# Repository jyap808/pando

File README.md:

# Pando Keyboard

Pando is a wired 58-key column-staggered split keyboard. It uses an integrated MCU design on the STM32 platform (STM32G0B1) with an IO expander (PCA9555) on the secondary half, connected over USB-C.

> [!NOTE]
> 📘 The **[Documentation pages](https://jyap808.github.io/pando)** contain a Build and Firmware guide.

> [!TIP]
> 🚀 Want one? Pre-assembled and PCB-tested kits are available on [Etsy](https://www.etsy.com/listing/4567044197/). Your support helps me keep this project open-source and encourages the development of new models!

## Features

- STM32G0B1KBT6 MCU (64 MHz Cortex-M0+, 144 KB SRAM)
- PCA9555 IO expander on the secondary half
- USB-C split communication with ESD protection on all ports
- Hotswap switch sockets
- Single-sided SMD components for hotplate soldering
- Vial firmware for keymap configuration
- Same key layout as the [Pando58](https://jyap808.github.io/pando58), but as an assembled PCB instead of a DIY kit

## Repository

| Directory | Description |
| --------- | ----------- |
| `kicad/` | Schematics and PCB (left, right, switch plates) |
| `firmware/` | QMK/Vial keyboard definition |
| `ergogen/` | Layout configuration and case/plate generation |
| `case/` | 3D printed case models (FreeCAD) |
| `docs/` | This project's documentation site (built with [Zensical](https://zensical.org/)) |

## Firmware

Pando runs [Vial](https://get.vial.today/) firmware. Precompiled builds are on [GitHub Releases](https://github.com/jyap808/pando/releases) — flash with `dfu-util`, or build from source with the keyboard definition in `firmware/keyboards/`. See [Installing Firmware](https://jyap808.github.io/pando/firmware/installing-firmware/) for details.

## License

[Pando Keyboard](https://github.com/jyap808/pando) © 2026 by [Julian Yap](https://julianyap.com/) is Open Hardware, licensed under [CERN-OHL-S v2](https://ohwr.org/cern_ohl_s_v2.txt). See [LICENSE](LICENSE).

The firmware in `firmware/` is licensed under the [GPL v2](https://www.gnu.org/licenses/old-licenses/gpl-2.0.html).

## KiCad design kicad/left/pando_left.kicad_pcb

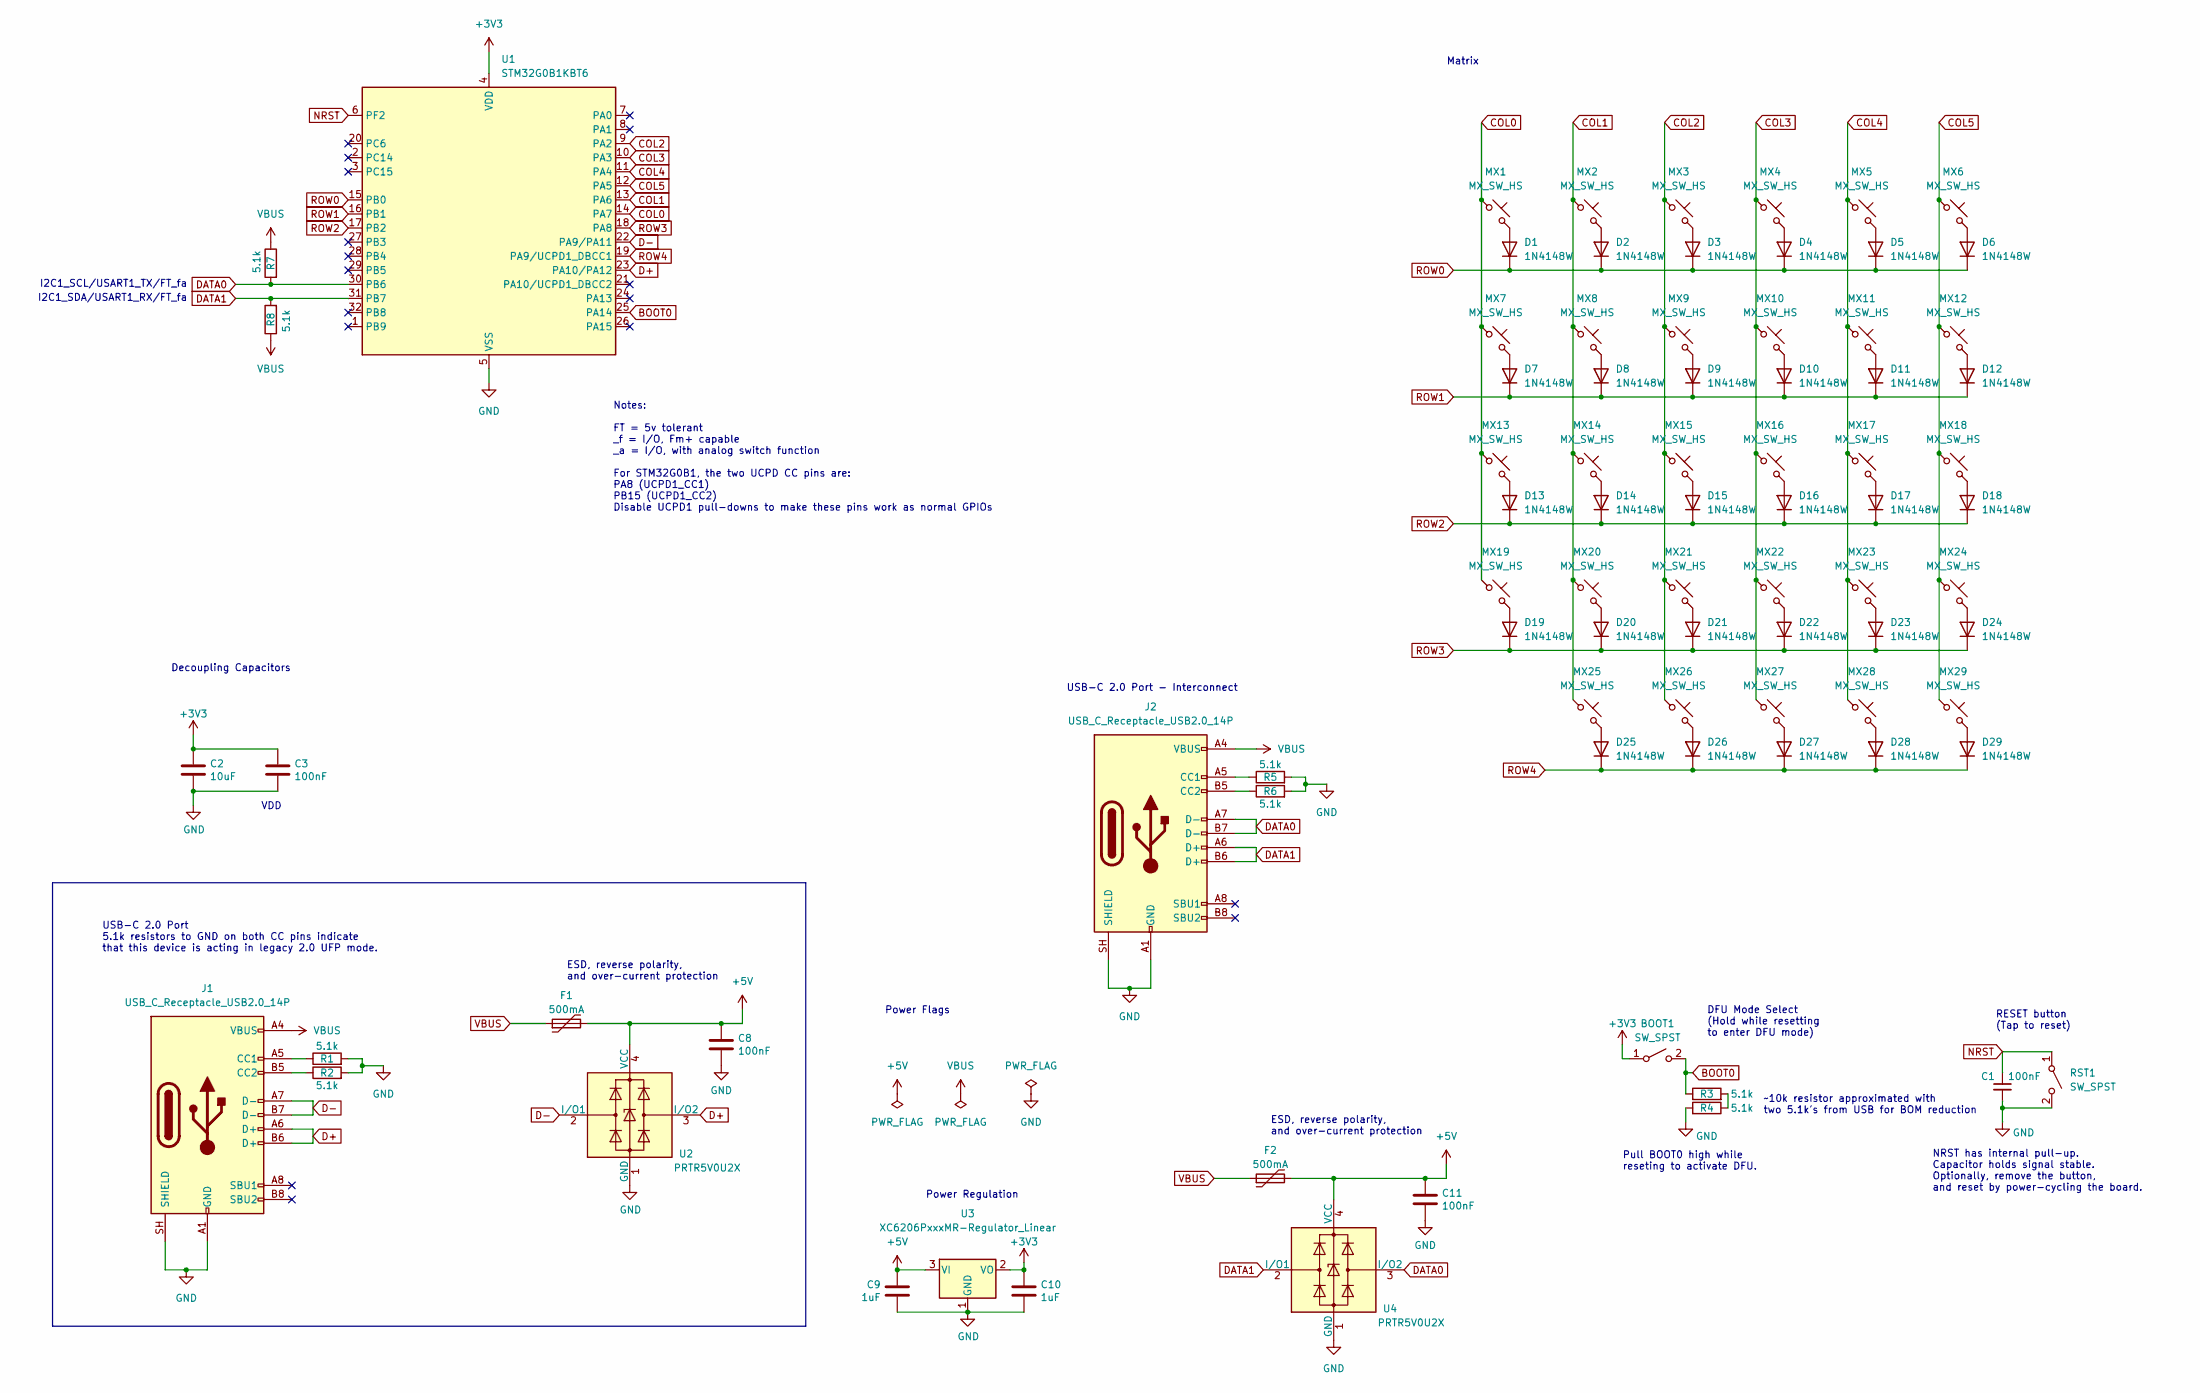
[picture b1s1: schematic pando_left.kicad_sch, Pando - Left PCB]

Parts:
BOOT1: SW_SPST; SW_SPST_TL3342; LCSC C318884
C1, C3, C8, C11: 100nF; C_0603_1608Metric; LCSC C14663
C2: 10uF; C_0603_1608Metric; LCSC C19702
C9, C10: 1uF; C_0603_1608Metric; LCSC C15849
D1, D2, D3, D4, D5, D6, D7, D8, D9, D10, D11, D12, D13, D14, D15, D16, D17, D18, D19, D20, D21, D22, D23, D24, D25, D26, D27, D28, D29: 1N4148W; D_SOD-123; LCSC C81598
F1, F2: 500mA; Fuse_1206_3216Metric; LCSC C135341
J1, J2: USB_C_Receptacle_USB2.0_14P; USB_C_Receptacle_HRO_TYPE-C-31-M-12; LCSC C165948
MX1, MX2, MX3, MX4, MX5, MX6, MX7, MX8, MX9, MX10, MX11, MX12, MX13, MX14, MX15, MX16, MX17, MX18, MX19, MX20, MX21, MX22, MX23, MX24, MX25, MX26, MX27, MX28, MX29: MX_SW_HS; SW_Hotswap_Kailh_MX; LCSC C41430893
R1, R2, R3, R4, R5, R6, R7, R8: 5.1k; R_0603_1608Metric; LCSC C2907114
RST1: SW_SPST; SW_SPST_TL3342; LCSC C318884
U1: STM32G0B1KBT6; LQFP-32_7x7mm_P0.8mm
U2, U4: PRTR5V0U2X; SOT-143; LCSC C2827688
U3: XC6206PxxxMR-Regulator_Linear; SOT-23-3; LCSC C5446

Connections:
+3V3: BOOT1.1 (A), C2.1, C3.1, C10.1, U1.4 (VDD), U3.2 (VO)
+5V: C8.1, C9.1, C11.1, F1.2, F2.2, U2.4 (VCC), U3.3 (VI), U4.4 (VCC)
BOOT0: BOOT1.2 (B), R3.1, U1.25 (PA14)
COL0: MX1.1, MX7.1, MX13.1, MX19.1, U1.14 (PA7)
COL1: MX2.1, MX8.1, MX14.1, MX20.1, MX25.1, U1.13 (PA6)
COL2: MX3.1, MX9.1, MX15.1, MX21.1, MX26.1, U1.9 (PA2)
COL3: MX4.1, MX10.1, MX16.1, MX22.1, MX27.1, U1.10 (PA3)
COL4: MX5.1, MX11.1, MX17.1, MX23.1, MX28.1, U1.11 (PA4)
COL5: MX6.1, MX12.1, MX18.1, MX24.1, MX29.1, U1.12 (PA5)
D+: J1.A6 (D+), J1.B6 (D+), U1.23 (PA10/PA12), U2.3 (I/O2)
D-: J1.A7 (D-), J1.B7 (D-), U1.22 (PA9/PA11), U2.2 (I/O1)
DATA0: J2.A7 (D-), J2.B7 (D-), R7.2, U1.30 (PB6), U4.3 (I/O2)
DATA1: J2.A6 (D+), J2.B6 (D+), R8.2, U1.31 (PB7), U4.2 (I/O1)
GND: C1.2, C2.2, C3.2, C8.2, C9.2, C10.2, C11.2, J1.A1 (GND), J1.A12 (GND), J1.B1 (GND), J1.B12 (GND), J1.SH (SHIELD), J2.A1 (GND), J2.A12 (GND), J2.B1 (GND), J2.B12 (GND), J2.SH (SHIELD), R1.2, R2.2, R4.2, R5.2, R6.2, RST1.2 (B), U1.5 (VSS), U2.1 (GND), U3.1 (GND), U4.1 (GND)
NRST: C1.1, RST1.1 (A), U1.6 (PF2)
unnamed: D1.2 (A), MX1.2
unnamed: D2.2 (A), MX2.2
unnamed: D3.2 (A), MX3.2
unnamed: D4.2 (A), MX4.2
unnamed: D5.2 (A), MX5.2
unnamed: D6.2 (A), MX6.2
unnamed: D7.2 (A), MX7.2
unnamed: D8.2 (A), MX8.2
unnamed: D9.2 (A), MX9.2
unnamed: D10.2 (A), MX10.2
unnamed: D11.2 (A), MX11.2
unnamed: D12.2 (A), MX12.2
unnamed: D13.2 (A), MX13.2
unnamed: D14.2 (A), MX14.2
unnamed: D15.2 (A), MX15.2
unnamed: D16.2 (A), MX16.2
unnamed: D17.2 (A), MX17.2
unnamed: D18.2 (A), MX18.2
unnamed: D19.2 (A), MX19.2
unnamed: D20.2 (A), MX20.2
unnamed: D21.2 (A), MX21.2
unnamed: D22.2 (A), MX22.2
unnamed: D23.2 (A), MX23.2
unnamed: D24.2 (A), MX24.2
unnamed: D25.2 (A), MX25.2
unnamed: D26.2 (A), MX26.2
unnamed: D27.2 (A), MX27.2
unnamed: D28.2 (A), MX28.2
unnamed: D29.2 (A), MX29.2
unnamed: J1.A5 (CC1), R1.1
unnamed: J1.B5 (CC2), R2.1
unnamed: J2.A5 (CC1), R5.1
unnamed: J2.B5 (CC2), R6.1
unnamed: R3.2, R4.1
ROW0: D1.1 (K), D2.1 (K), D3.1 (K), D4.1 (K), D5.1 (K), D6.1 (K), U1.15 (PB0)
ROW1: D7.1 (K), D8.1 (K), D9.1 (K), D10.1 (K), D11.1 (K), D12.1 (K), U1.16 (PB1)
ROW2: D13.1 (K), D14.1 (K), D15.1 (K), D16.1 (K), D17.1 (K), D18.1 (K), U1.17 (PB2)
ROW3: D19.1 (K), D20.1 (K), D21.1 (K), D22.1 (K), D23.1 (K), D24.1 (K), U1.18 (PA8)
ROW4: D25.1 (K), D26.1 (K), D27.1 (K), D28.1 (K), D29.1 (K), U1.19 (PA9/UCPD1_DBCC1)
VBUS: F1.1, F2.1, J1.A4 (VBUS), J1.A9 (VBUS), J1.B4 (VBUS), J1.B9 (VBUS), J2.A4 (VBUS), J2.A9 (VBUS), J2.B4 (VBUS), J2.B9 (VBUS), R7.1, R8.1

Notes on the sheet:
RESET button (Tap to reset)
USB-C 2.0 Port - Interconnect
Pull BOOT0 high while reseting to activate DFU.
Notes: FT = 5v tolerant _f = I/O, Fm+ capable _a = I/O, with analog switch function For STM32G0B1, the two UCPD CC pins are: PA8 (UCPD1_CC1) PB15 (UCPD1_CC2) Disable UCPD1 pull-downs to make these pins work as normal GPIOs
Power Regulation
ESD, reverse polarity, and over-current protection
NRST has internal pull-up. Capacitor holds signal stable. Optionally, remove the button, and reset by power-cycling the board.
USB-C 2.0 Port 5.1k resistors to GND on both CC pins indicate that this device is acting in legacy 2.0 UFP mode.
Power Flags
I2C1_SCL/USART1_TX/FT_fa
VDD
~10k resistor approximated with two 5.1k's from USB for BOM reduction
I2C1_SDA/USART1_RX/FT_fa
Decoupling Capacitors
DFU Mode Select (Hold while resetting to enter DFU mode)
Matrix

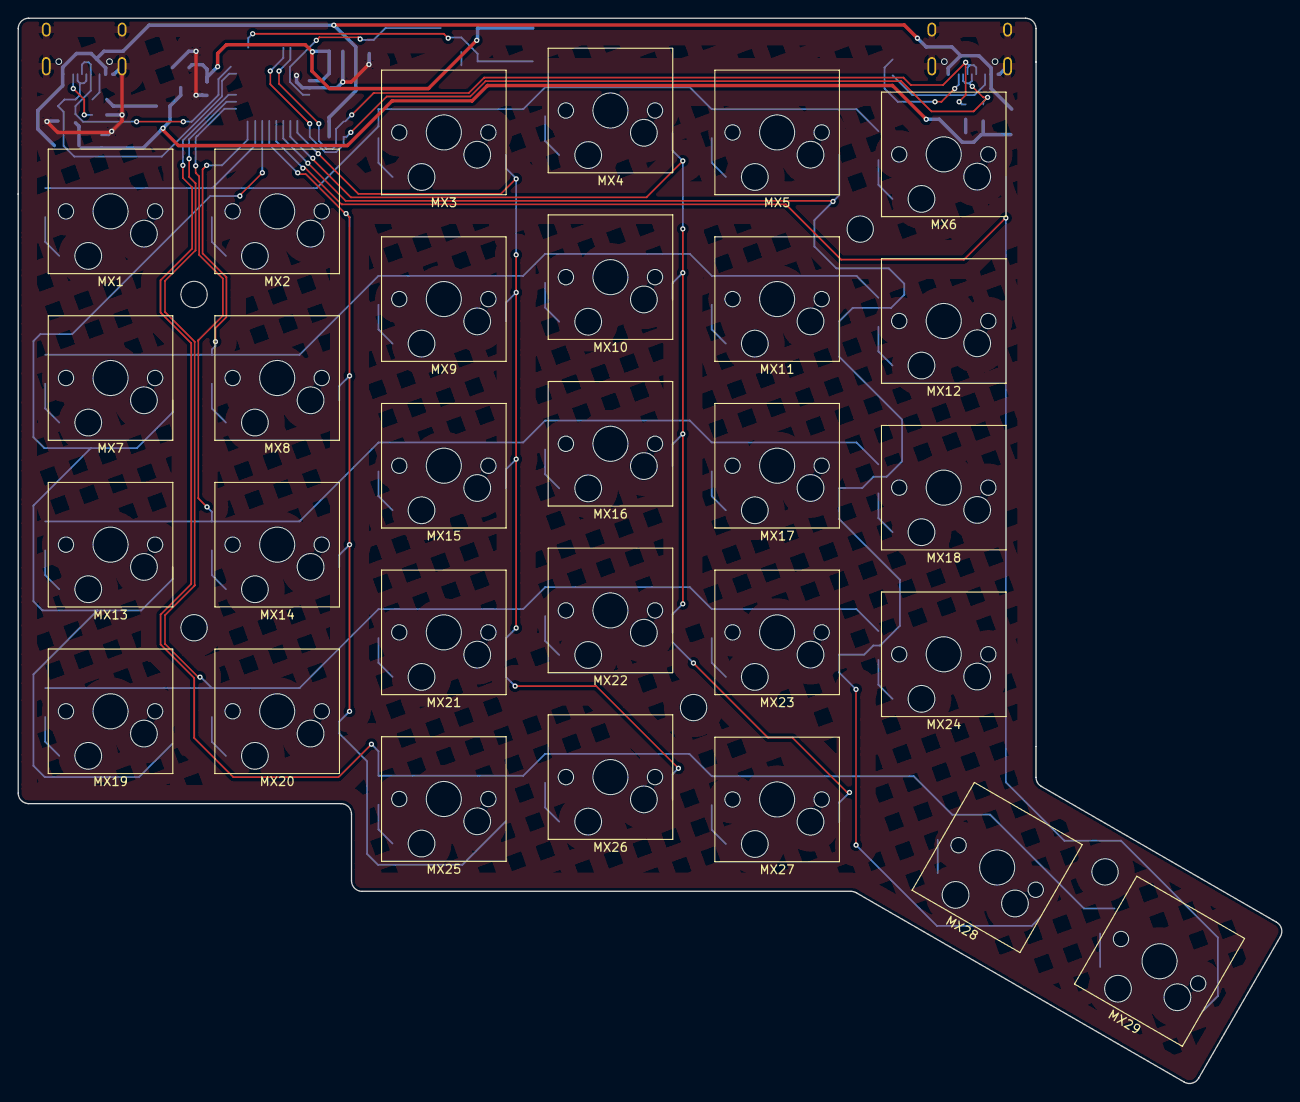
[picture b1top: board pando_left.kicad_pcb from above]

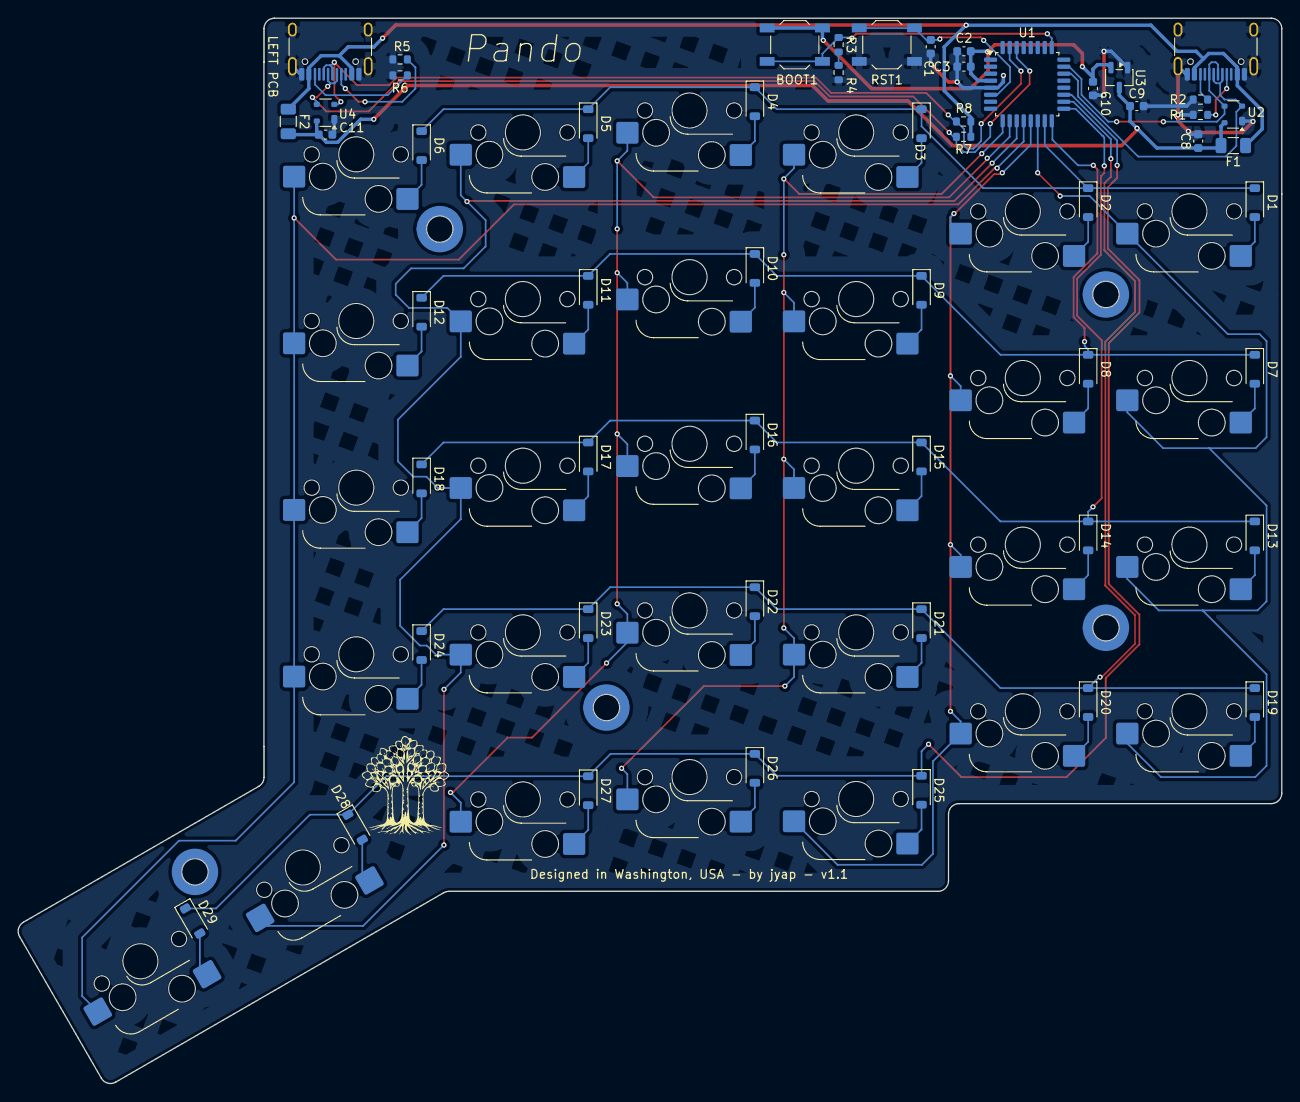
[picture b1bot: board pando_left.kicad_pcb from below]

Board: 2 copper layers, 144.1 x 121.5 mm, 89 parts (60 on the bottom side), 55 nets.

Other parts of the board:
H1, H2, H3, H4, H5: Mounting_Wuerth_WA-SMSI-M2_H3.5mm_9774035243
Logo1: Pando logo

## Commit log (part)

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2026-06-11 devenv.lock: update devenv lockfile
2026-06-11 Initial commit of WIP Ergogen config
2026-06-11 Plate outline fix
2026-06-11 Rename stm32_poc to pando, add pando_plate PCB
2026-06-11 Place Button switch footprints
2026-06-11 Place MCU and Resistor footprints
2026-06-12 Place more footprints. Minor fixes.
2026-06-12 Add capacitor placeholders
2026-06-12 Add placeholder footprint module
2026-06-13 Finishing off the right hand side components
2026-06-13 Add logo footprint, text labels, and SVG gen script
2026-06-16 Add inner mounting hole points and plated footprints
2026-06-16 feat: add KiCad design files for pando split keyboard
    Left and right PCB schematics, layouts, plate design, mounting hole footprint and BOM files
2026-06-18 feat: add case outlines, sandwich mounts and KiCad fp-lib-tables
2026-06-19 ergogen/config.yaml: adjust shift values for improved precision
2026-06-19 Remove Logo from interactive BOM
